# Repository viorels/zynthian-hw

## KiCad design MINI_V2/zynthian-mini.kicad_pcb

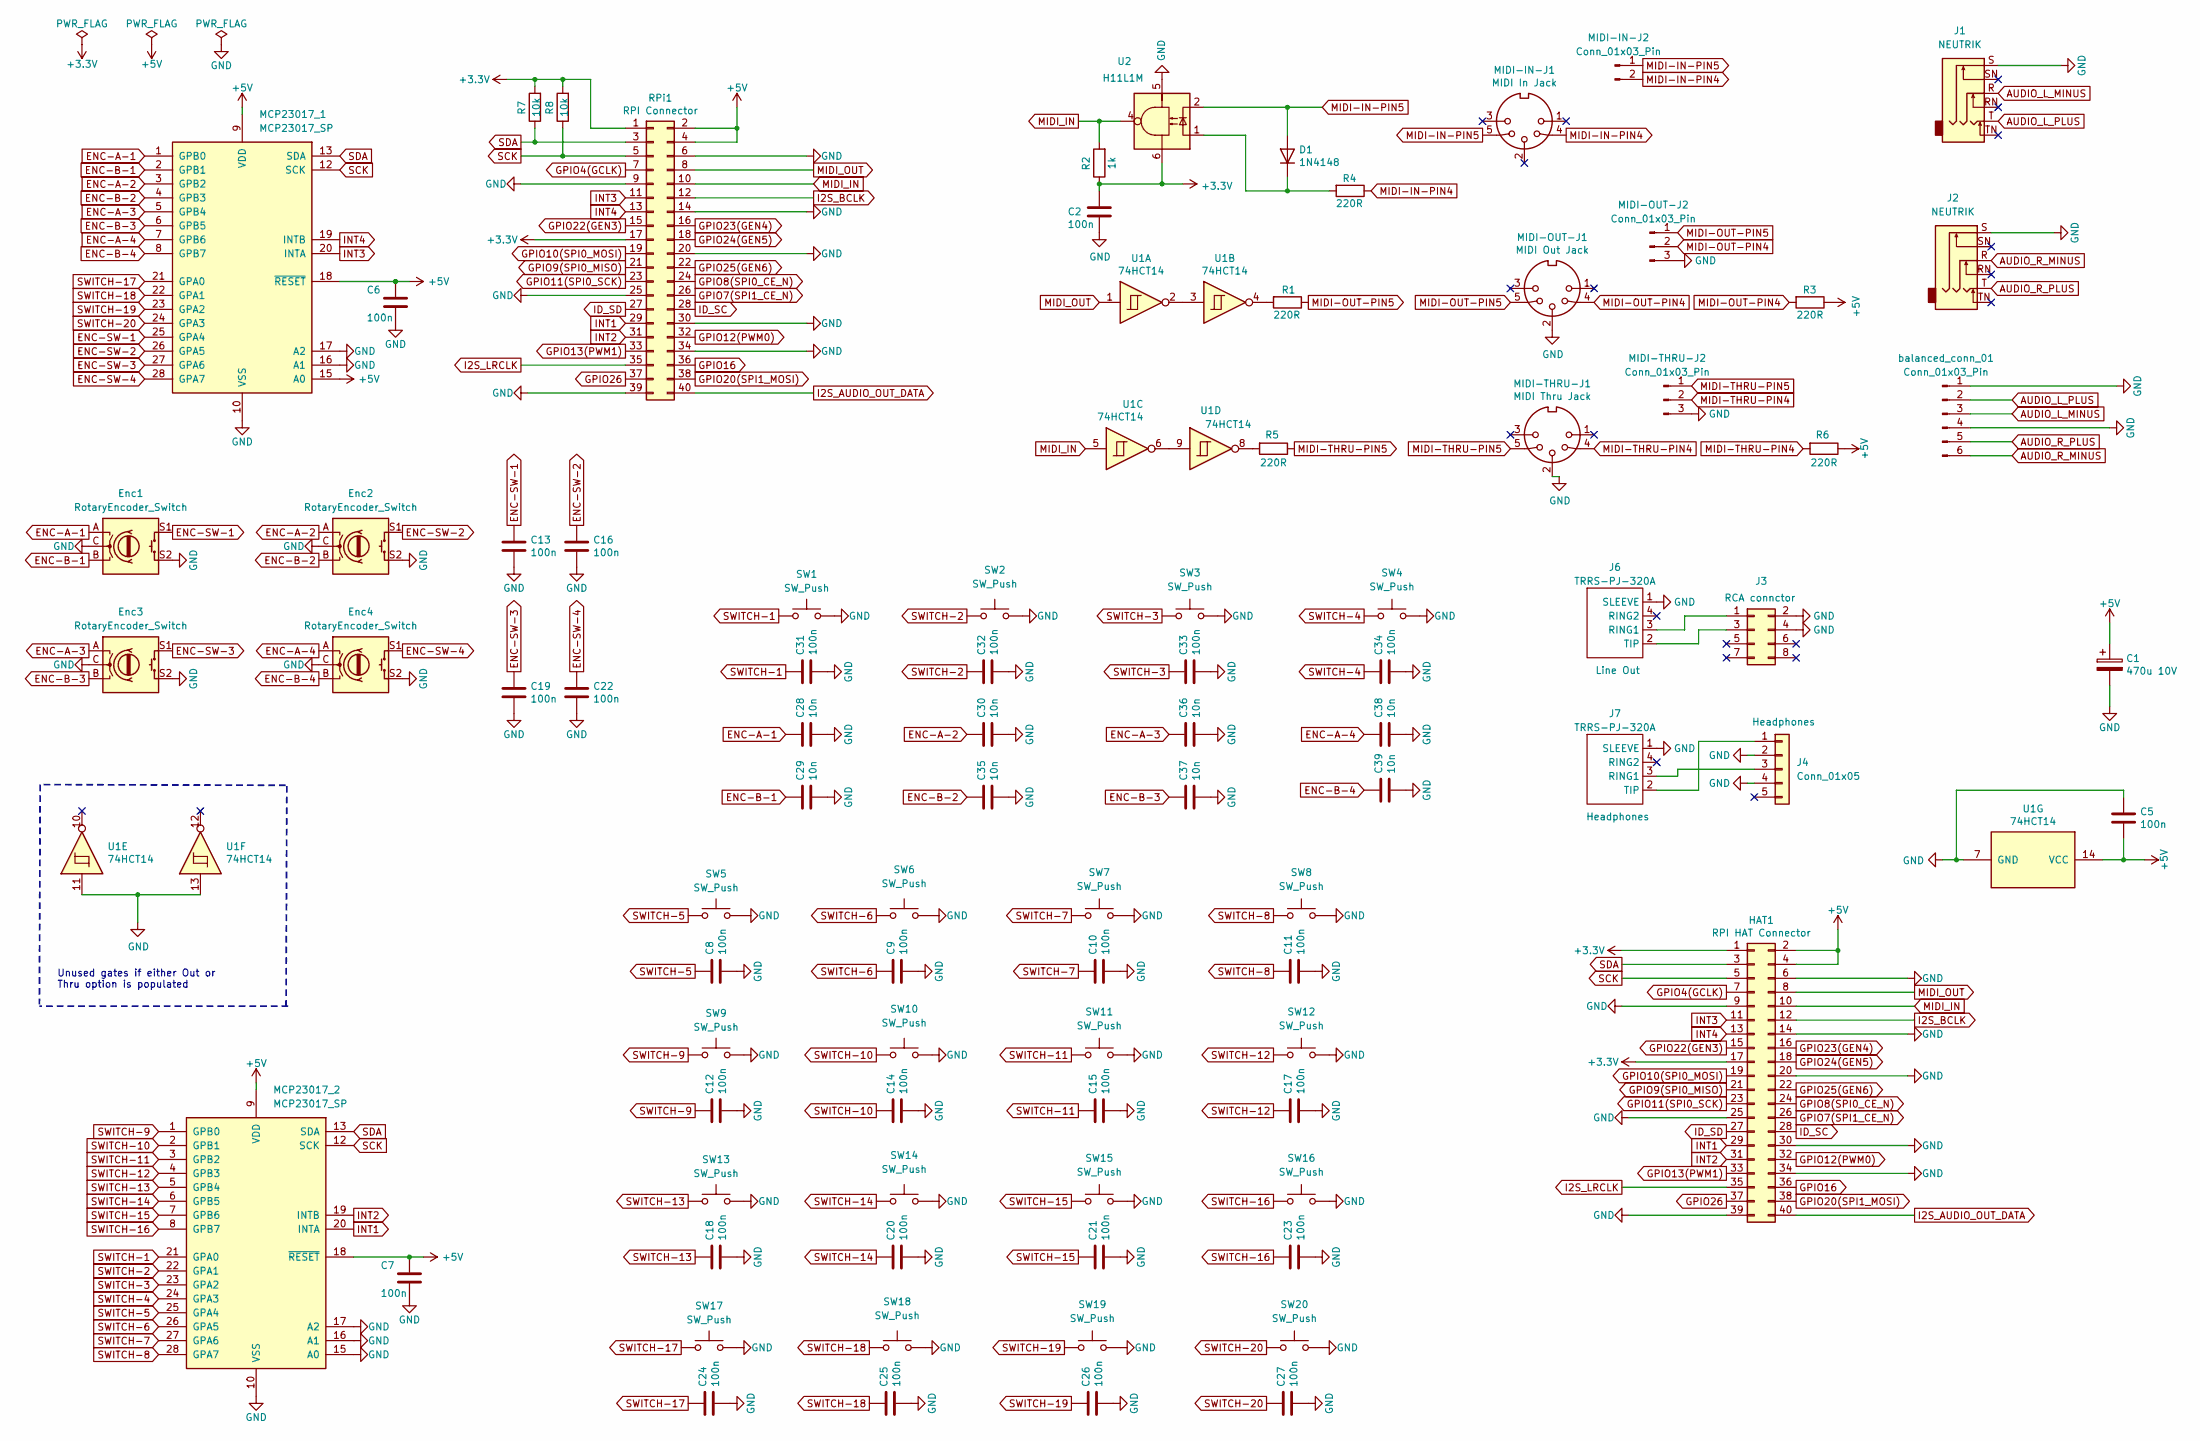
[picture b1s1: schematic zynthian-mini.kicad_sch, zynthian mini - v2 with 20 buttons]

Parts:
C1: 470u 10V; CP_Radial_D8.0mm_P3.50mm
C2, C5, C6, C7: 100n; C_Rect_L7.0mm_W2.0mm_P5.00mm
C8, C9, C10, C11, C12, C13, C14, C15, C16, C17, C18, C19, C20, C21, C22, C23, C24, C25, C26, C27, C31, C32, C33, C34: 100n; C_Rect_L4.0mm_W2.5mm_P2.50mm
C28, C29, C30, C35, C36, C37, C38, C39: 10n; C_Rect_L4.0mm_W2.5mm_P2.50mm
D1: 1N4148; D_DO-35_SOD27_P7.62mm_Horizontal
Enc1, Enc2, Enc3, Enc4: RotaryEncoder_Switch; RotaryEncoder_Alps_EC12E-Switch_Vertical_H20mm
HAT1: RPI HAT Connector; raspberry pi 4
J1, J2: NEUTRIK; Jack_6.35mm_Neutrik_NMJ6HFD2_Horizontal
J3: Conn_02x04_Odd_Even; PinHeader_2x04_P2.54mm_Vertical
J4: Conn_01x05; PinHeader_1x05_P2.54mm_Vertical
J6, J7: TRRS-PJ-320A; MPN TRRS-PJ-320A
MCP23017_1, MCP23017_2: MCP23017_SP; DIP-28_W7.62mm
MIDI-IN-J1: MIDI In Jack; MultiDIN5
MIDI-IN-J2: Conn_01x03_Pin; PinHeader_1x02_P2.54mm_Vertical
MIDI-OUT-J1: MIDI Out Jack; MultiDIN5
MIDI-OUT-J2: Conn_01x03_Pin; PinHeader_1x03_P2.54mm_Vertical
MIDI-THRU-J1: MIDI Thru Jack; MultiDIN5
MIDI-THRU-J2: Conn_01x03_Pin; PinHeader_1x03_P2.54mm_Vertical
R1, R3, R4, R5, R6: 220R; R_Axial_DIN0207_L6.3mm_D2.5mm_P7.62mm_Horizontal
R2: 1k; R_Axial_DIN0207_L6.3mm_D2.5mm_P7.62mm_Horizontal
R7, R8: 10k; R_Axial_DIN0207_L6.3mm_D2.5mm_P7.62mm_Horizontal
RPi1: RPI Connector; raspberry pi 4 HAT
SW1, SW2, SW3, SW4, SW5, SW6, SW7, SW8, SW9, SW10, SW11, SW12, SW13, SW14, SW15, SW16, SW17, SW18, SW19, SW20: SW_Push; push-button-13mm
U1: 74HCT14; DIP-14_W7.62mm
U2: H11L1M; DIP-6_W7.62mm
balanced_conn_01: Conn_01x03_Pin; PinHeader_1x06_P2.54mm_Vertical

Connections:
AUDIO_L_MINUS: J1.R, balanced_conn_01.3
AUDIO_L_PLUS: J1.T, balanced_conn_01.2
AUDIO_R_MINUS: J2.R, balanced_conn_01.6
AUDIO_R_PLUS: J2.T, balanced_conn_01.5
ENC-A-1: C28.1, Enc1.A, MCP23017_1.1 (GPB0)
ENC-A-2: C30.1, Enc2.A, MCP23017_1.3 (GPB2)
ENC-A-3: C36.1, Enc3.A, MCP23017_1.5 (GPB4)
ENC-A-4: C38.1, Enc4.A, MCP23017_1.7 (GPB6)
ENC-B-1: C29.1, Enc1.B, MCP23017_1.2 (GPB1)
ENC-B-2: C35.1, Enc2.B, MCP23017_1.4 (GPB3)
ENC-B-3: C37.1, Enc3.B, MCP23017_1.6 (GPB5)
ENC-B-4: C39.1, Enc4.B, MCP23017_1.8 (GPB7)
ENC-SW-1: C13.1, Enc1.S1, MCP23017_1.25 (GPA4)
ENC-SW-2: C16.1, Enc2.S1, MCP23017_1.26 (GPA5)
ENC-SW-3: C19.1, Enc3.S1, MCP23017_1.27 (GPA6)
ENC-SW-4: C22.1, Enc4.S1, MCP23017_1.28 (GPA7)
GPIO4(GCLK): HAT1.7, RPi1.7
GPIO7(SPI1_CE_N): HAT1.26, RPi1.26
GPIO8(SPI0_CE_N): HAT1.24, RPi1.24
GPIO9(SPI0_MISO): HAT1.21, RPi1.21
GPIO10(SPI0_MOSI): HAT1.19, RPi1.19
GPIO11(SPI0_SCK): HAT1.23, RPi1.23
GPIO12(PWM0): HAT1.32, RPi1.32
GPIO13(PWM1): HAT1.33, RPi1.33
GPIO16: HAT1.36, RPi1.36
GPIO20(SPI1_MOSI): HAT1.38, RPi1.38
GPIO22(GEN3): HAT1.15, RPi1.15
GPIO23(GEN4): HAT1.16, RPi1.16
GPIO24(GEN5): HAT1.18, RPi1.18
GPIO25(GEN6): HAT1.22, RPi1.22
GPIO26: HAT1.37, RPi1.37
I2S_AUDIO_OUT_DATA: HAT1.40, RPi1.40
I2S_BCLK: HAT1.12, RPi1.12
I2S_LRCLK: HAT1.35, RPi1.35
ID_SC: HAT1.28, RPi1.28
ID_SD: HAT1.27, RPi1.27
INT1: HAT1.29, MCP23017_2.20 (INTA), RPi1.29
INT2: HAT1.31, MCP23017_2.19 (INTB), RPi1.31
INT3: HAT1.11, MCP23017_1.20 (INTA), RPi1.11
INT4: HAT1.13, MCP23017_1.19 (INTB), RPi1.13
MIDI-IN-PIN4: MIDI-IN-J1.4, MIDI-IN-J2.2, R4.1
MIDI-IN-PIN5: D1.2 (A), MIDI-IN-J1.5, MIDI-IN-J2.1, U2.2
MIDI-OUT-PIN4: MIDI-OUT-J1.4, MIDI-OUT-J2.2, R3.2
MIDI-OUT-PIN5: MIDI-OUT-J1.5, MIDI-OUT-J2.1, R1.1
MIDI-THRU-PIN4: MIDI-THRU-J1.4, MIDI-THRU-J2.2, R6.2
MIDI-THRU-PIN5: MIDI-THRU-J1.5, MIDI-THRU-J2.1, R5.1
MIDI_IN: HAT1.10, R2.2, RPi1.10, U1.5, U2.4
MIDI_OUT: HAT1.8, RPi1.8, U1.1
unnamed: D1.1 (K), R4.2, U2.1
unnamed: J3.1, J6.3 (RING1)
unnamed: J3.3, J6.2 (TIP)
unnamed: J4.1, J7.2 (TIP)
unnamed: J4.3, J7.3 (RING1)
unnamed: R1.2, U1.4
unnamed: R5.2, U1.8
unnamed: U1.2, U1.3
unnamed: U1.6, U1.9
SCK: HAT1.5, MCP23017_1.12 (SCK), MCP23017_2.12 (SCK), R8.1, RPi1.5
SDA: HAT1.3, MCP23017_1.13 (SDA), MCP23017_2.13 (SDA), R7.1, RPi1.3
SWITCH-1: C31.1, MCP23017_2.21 (GPA0), SW1.1
SWITCH-2: C32.1, MCP23017_2.22 (GPA1), SW2.1
SWITCH-3: C33.1, MCP23017_2.23 (GPA2), SW3.1
SWITCH-4: C34.1, MCP23017_2.24 (GPA3), SW4.1
SWITCH-5: C8.1, MCP23017_2.25 (GPA4), SW5.1
SWITCH-6: C9.1, MCP23017_2.26 (GPA5), SW6.1
SWITCH-7: C10.1, MCP23017_2.27 (GPA6), SW7.1
SWITCH-8: C11.1, MCP23017_2.28 (GPA7), SW8.1
SWITCH-9: C12.1, MCP23017_2.1 (GPB0), SW9.1
SWITCH-10: C14.1, MCP23017_2.2 (GPB1), SW10.1
SWITCH-11: C15.1, MCP23017_2.3 (GPB2), SW11.1
SWITCH-12: C17.1, MCP23017_2.4 (GPB3), SW12.1
SWITCH-13: C18.1, MCP23017_2.5 (GPB4), SW13.1
SWITCH-14: C20.1, MCP23017_2.6 (GPB5), SW14.1
SWITCH-15: C21.1, MCP23017_2.7 (GPB6), SW15.1
SWITCH-16: C23.1, MCP23017_2.8 (GPB7), SW16.1
SWITCH-17: C24.1, MCP23017_1.21 (GPA0), SW17.1
SWITCH-18: C25.1, MCP23017_1.22 (GPA1), SW18.1
SWITCH-19: C26.1, MCP23017_1.23 (GPA2), SW19.1
SWITCH-20: C27.1, MCP23017_1.24 (GPA3), SW20.1

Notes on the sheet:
Unused gates if either Out or Thru option is populated

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
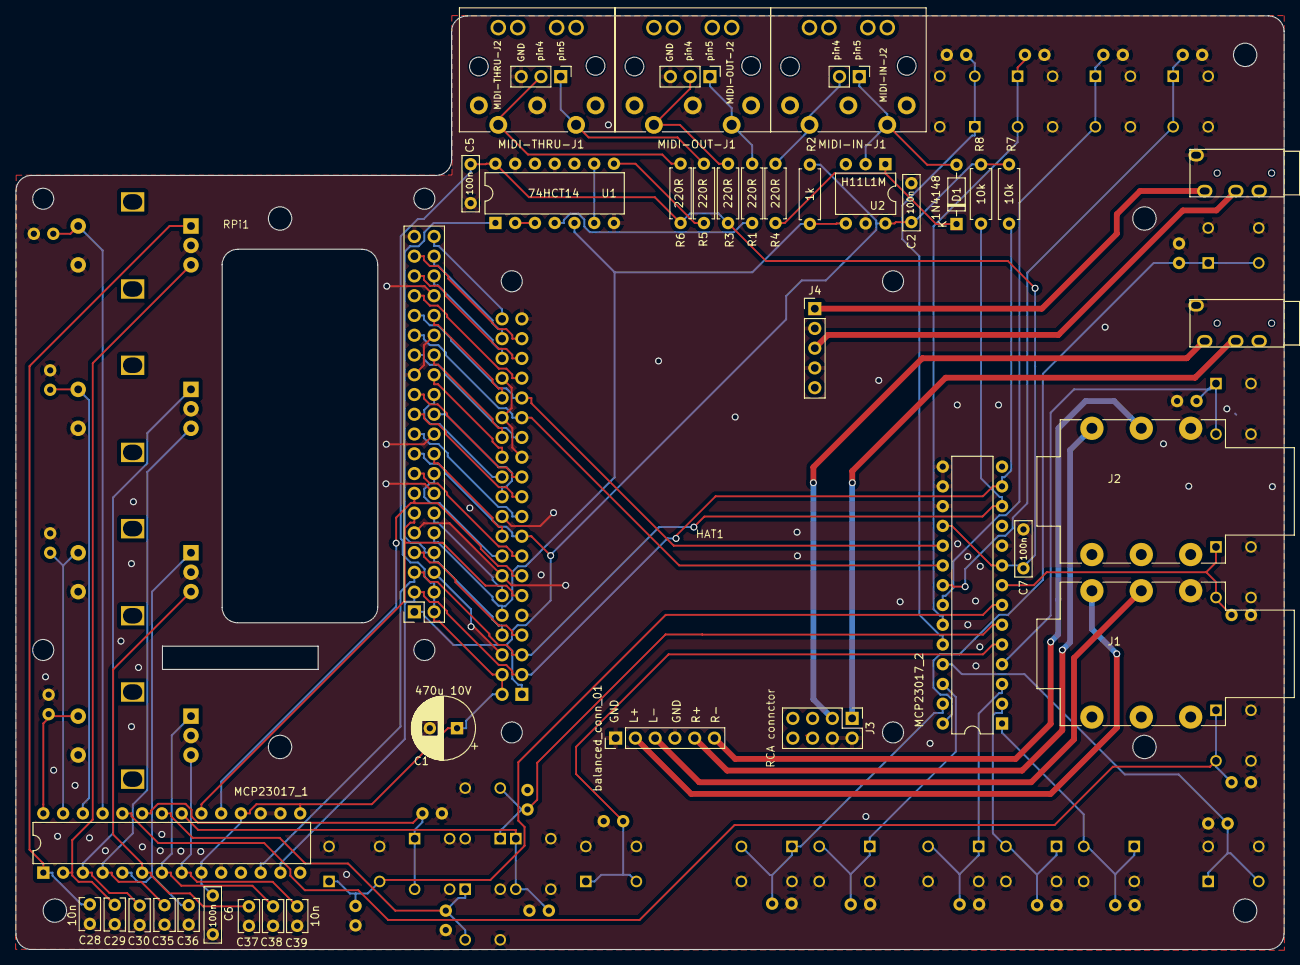
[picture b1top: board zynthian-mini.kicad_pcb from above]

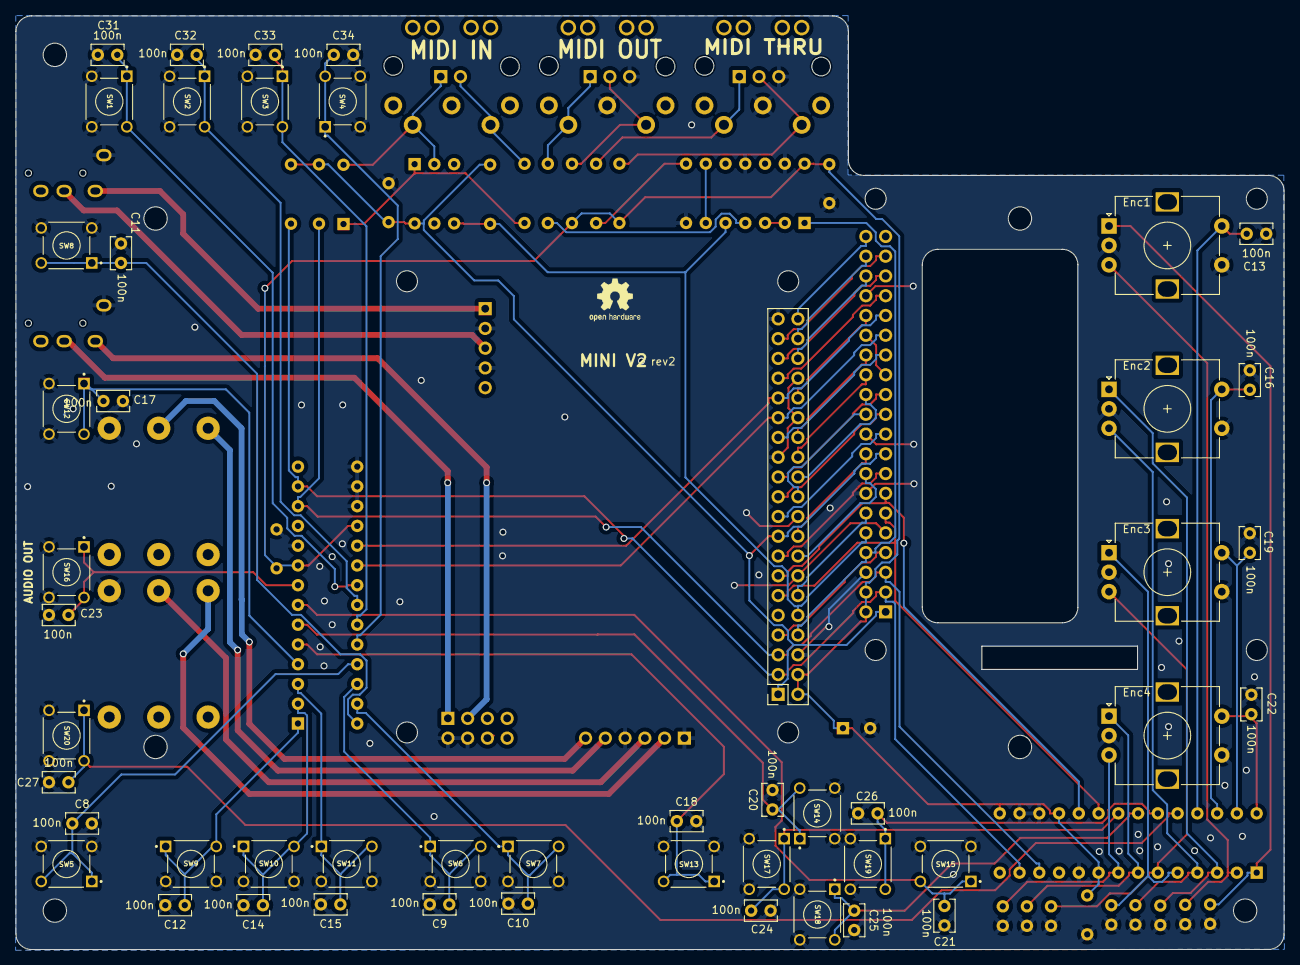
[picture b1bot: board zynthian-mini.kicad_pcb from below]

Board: 2 copper layers, 163.0 x 120.0 mm, 91 parts (49 on the bottom side), 82 nets.

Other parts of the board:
logo1: MINI V2; Zynthian Logo Mask
screen: aliexpress 5 inch screen

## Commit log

2025-03-12 removed PCM sound card, resized pin connector from 3 to 6 pins
2025-03-13 2x6.3 connectors done, trying one mini jack
2025-03-14 add TRRS jack symbol and footprint, connect to line out
2025-03-14 small cleanup for old traces, add 2nd mini jack
2025-03-15 finished schematic, added headphones jack
2025-03-15 finished all tracks, but pins not aligned
2025-03-15 aligned connectors, rerouted; scree hole is covered by L-bal jack
2025-03-16 moved 6.3 jacks to free screen hole
2025-03-16 fixed "design rules checker"
2025-03-16 thicker audio signals
